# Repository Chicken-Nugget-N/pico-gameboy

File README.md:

# pico-gameboy
For week 5 of half life I will be making a raspberry pi pico gameboy. I found a really cool repo that uses peanut GB to emulate GB games onto a pico, so I am going to use that. I'm also going to be creating a PCB to connect all of my components instead of just using a bunch of jumper wires. I think I'll cad a case myself, just to customize it.
I worked on the cad in relation to the parts provided by the Peanut GB fork for the pico.
super excited to play pokemon!!

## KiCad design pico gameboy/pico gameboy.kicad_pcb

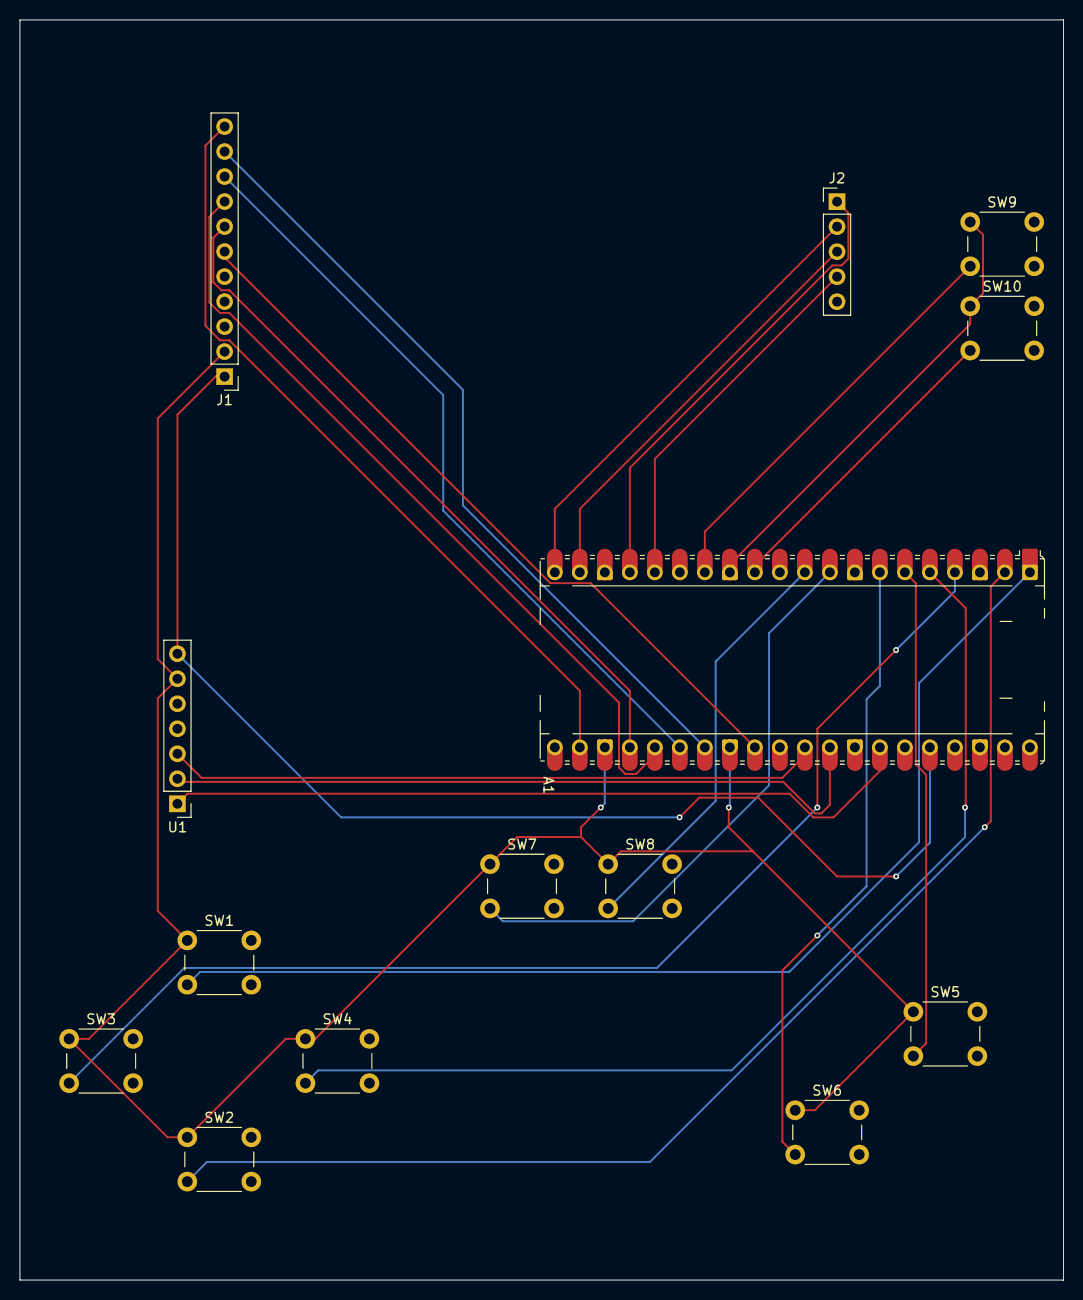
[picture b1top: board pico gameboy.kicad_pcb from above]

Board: 2 copper layers, 106.0 x 128.0 mm, 14 parts (0 on the bottom side), 25 nets.

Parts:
A1: RaspberryPi_Pico; RaspberryPi_Pico_Common_Unspecified
J1: Conn_01x11; PinHeader_1x11_P2.54mm_Vertical
J2: Conn_01x05; PinHeader_1x05_P2.54mm_Vertical
SW1, SW2, SW3, SW4, SW5, SW6, SW7, SW8, SW9, SW10: SW_MEC_5E; SW_PUSH_6mm_new
U1: MAX98357A; PinHeader_1x07_P2.54mm_Vertical

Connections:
+3.3V: A1.36 (3V3), J1.1, U1.7 (VDD)
/A: A1.6 (GPIO4), SW5.4 (A)
/B: A1.7 (GPIO5), SW6.4 (A)
/BCLK: A1.32 (GPIO27_ADC1), U1.16 (BCLK)
/CLK: A1.24 (GPIO18), J1.7
/CS: A1.22 (GPIO17), J1.11
/DIN: A1.31 (GPIO26_ADC0), U1.1 (DIN)
/DOWN: A1.2 (GPIO1), SW2.4 (A)
/LEFT: A1.4 (GPIO2), SW3.4 (A)
/LRC: A1.34 (GPIO28_ADC2), U1.14 (LRCLK)
/NC: A1.29 (GPIO22), J1.6
/RIGHT: A1.5 (GPIO3), SW4.4 (A)
/RS: A1.26 (GPIO20), J1.9
/RST: A1.27 (GPIO21), J1.10
/SDA: A1.25 (GPIO19), J1.8
/SD_CS: A1.17 (GPIO13), J2.1
/SD_MISO: A1.16 (GPIO12), J2.4
/SD_MOSI: A1.20 (GPIO15), J2.2
/SD_SCK: A1.19 (GPIO14), J2.3
/SEL: A1.9 (GPIO6), SW7.4 (A)
/START: A1.10 (GPIO7), SW8.4 (A)
/UP: A1.1 (GPIO0), SW1.4 (A)
/VOL-DW: A1.12 (GPIO9), SW10.4 (A)
/VOL-UP: A1.14 (GPIO10), SW9.4 (A)
GND: A1.3 (GND), A1.8 (GND), A1.13 (GND), A1.18 (GND), A1.23 (GND), A1.28 (GND), A1.38 (GND), J1.2, SW1.1, SW2.1, SW3.1, SW4.1, SW5.1, SW6.1, SW7.1, SW8.1, SW9.1, SW10.1, U1.3 (GND)
